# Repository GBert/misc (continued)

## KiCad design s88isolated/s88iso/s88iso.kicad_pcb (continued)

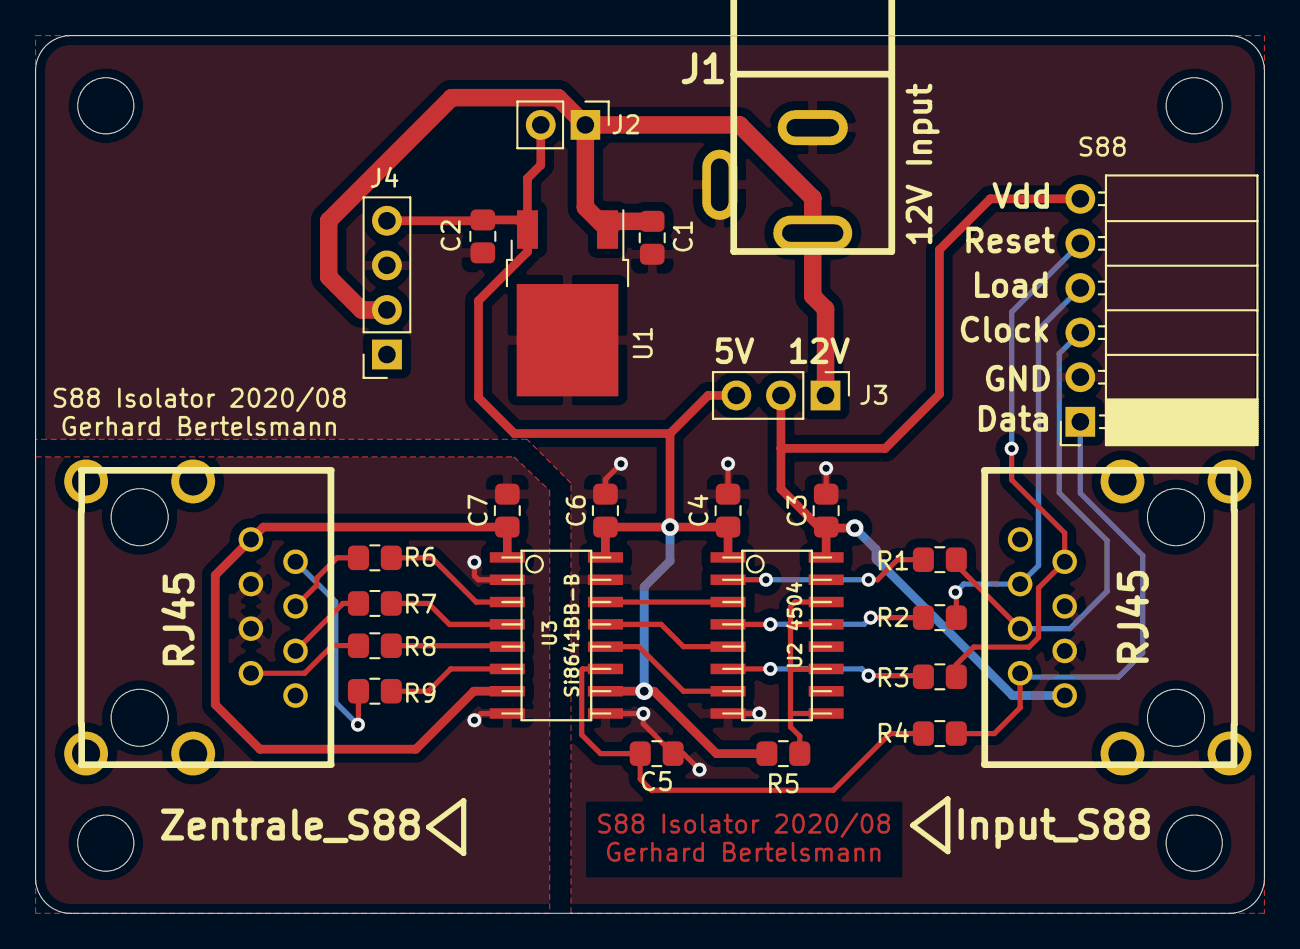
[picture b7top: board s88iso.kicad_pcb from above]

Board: 2 copper layers, 70.0 x 50.0 mm, 26 parts (0 on the bottom side), 26 nets.

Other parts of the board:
Input_S88: RJ45; megb8-8-Uni
Zentrale_S88: RJ45; megb8-8-Uni

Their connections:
+5V: Zentrale_S88.1; also elsewhere on the board
/Clock: Zentrale_S88.4; also elsewhere on the board
/Clock': Input_S88.4; also elsewhere on the board
/Data: Zentrale_S88.2; also elsewhere on the board
/Data': Input_S88.2; also elsewhere on the board
/PSLoad: Zentrale_S88.6; also elsewhere on the board
/PSLoad': Input_S88.6; also elsewhere on the board
/Reset: Zentrale_S88.7; also elsewhere on the board
/Reset': Input_S88.7; also elsewhere on the board
GND: Zentrale_S88.3, Zentrale_S88.5; also elsewhere on the board
GNDD: Input_S88.3, Input_S88.5; also elsewhere on the board
VDD: Input_S88.1; also elsewhere on the board

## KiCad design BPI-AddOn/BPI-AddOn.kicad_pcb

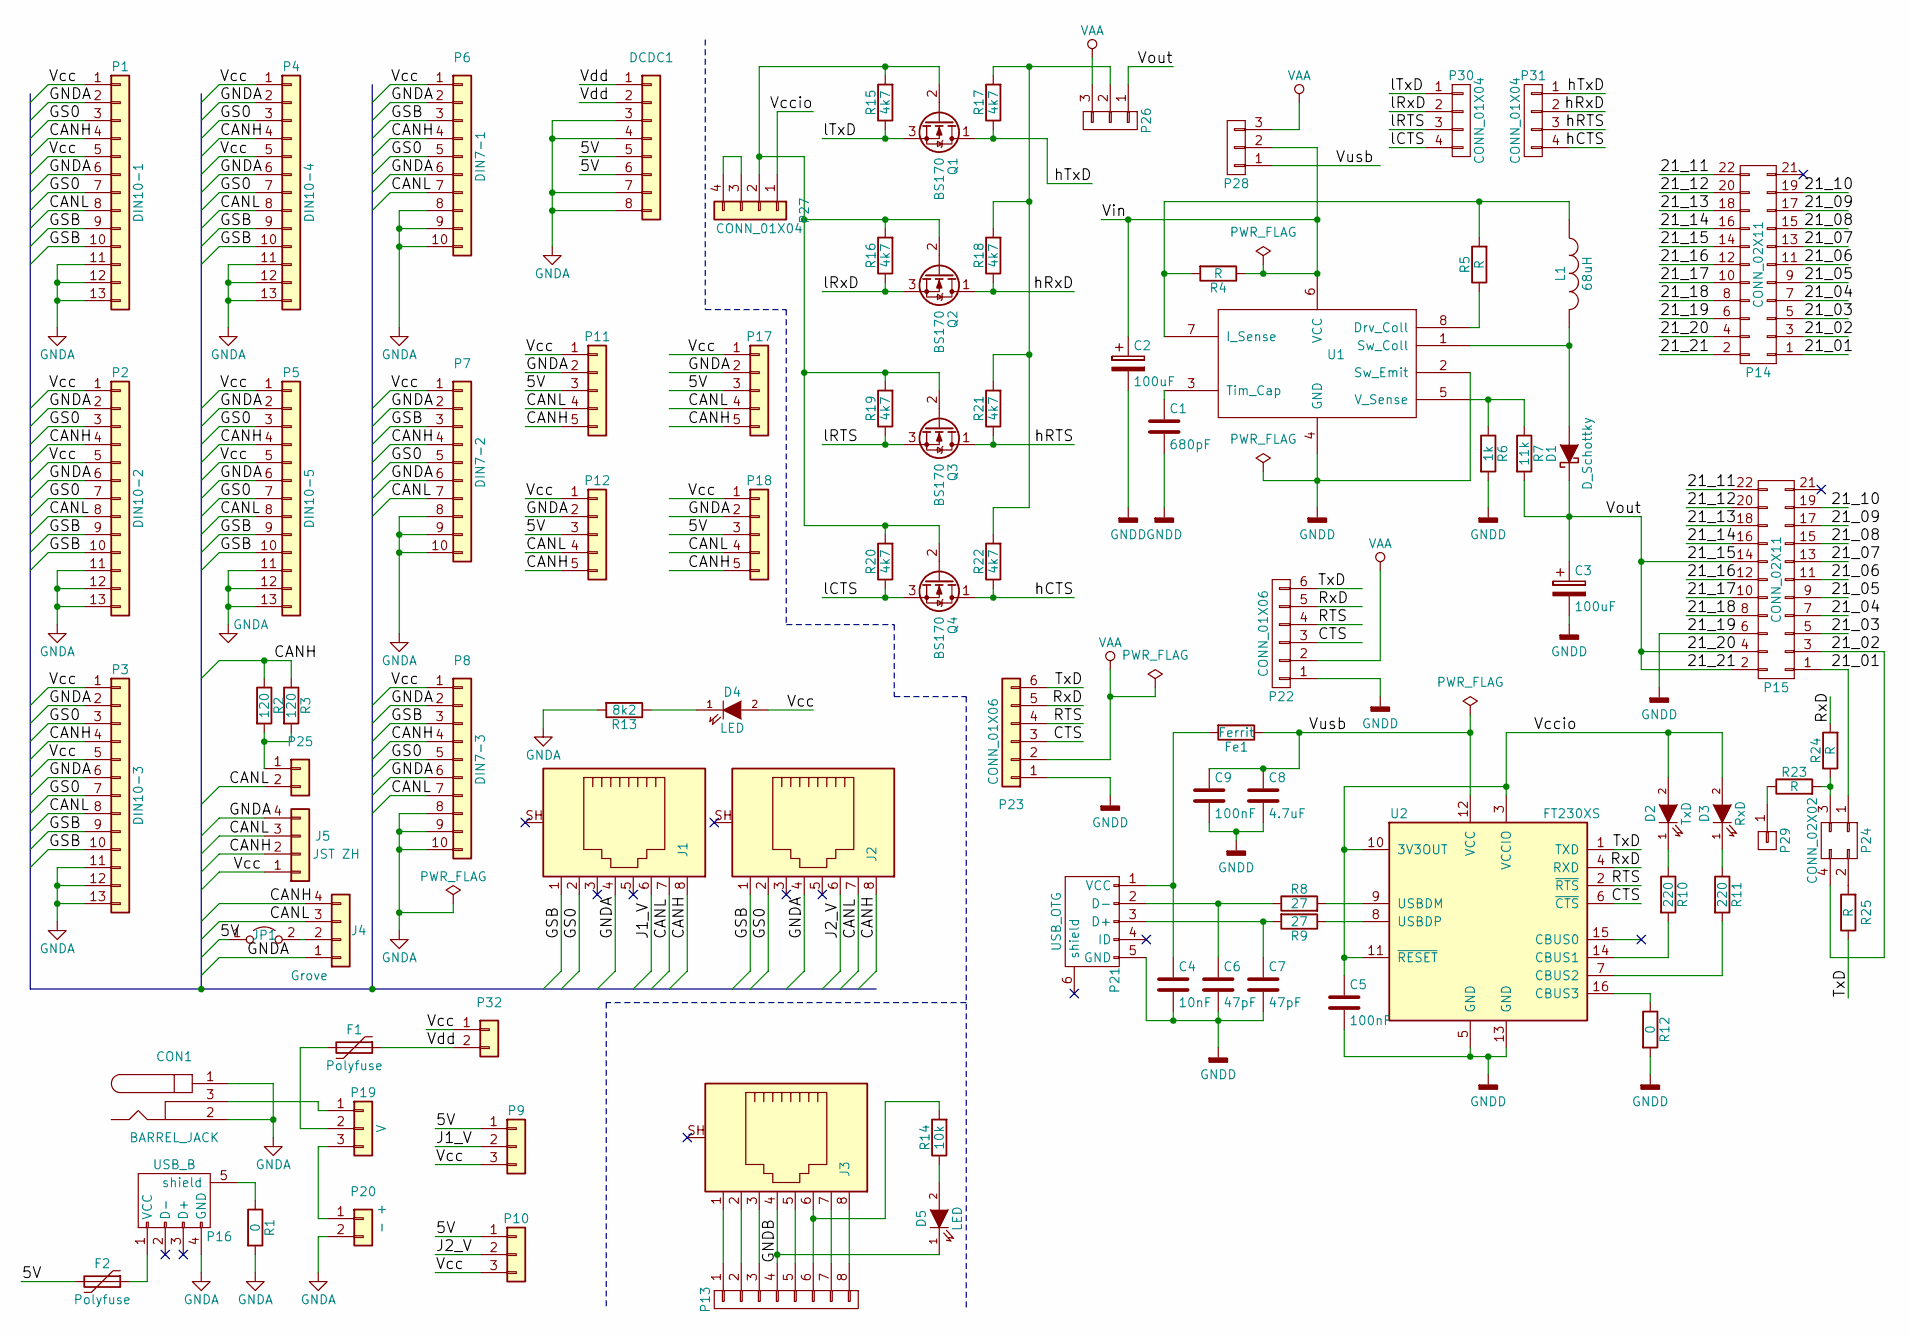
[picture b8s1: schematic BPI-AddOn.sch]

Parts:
C1: 680pF; cnp_3mm_disc
C2, C3: 100uF; CP_5x11mm
C4: 10nF; R_0805_HandSoldering
C5, C9: 100nF; R_0805_HandSoldering
C6, C7: 47pF; R_0805_HandSoldering
C8: 4.7uF; R_0805_HandSoldering
CON1: BARREL_JACK; dc_socket
D1: D_Schottky; Diode_DO-35_SOD27_Horizontal_RM10
D2: TxD; LED_0805
D3: RxD; LED_0805
D4, D5: LED; LED-5MM
DCDC1: DCDC-Conevrter; DCDC
F1, F2: Polyfuse; cnp_6mm_disc
Fe1: Ferrit; R_0805_HandSoldering
J1, J2, J3: RJ45; megb8-8
J4: Grove; grove-straight
J5: JST ZH; B4B-ZR
JP1: Jumper_2_Open; PinHeader_1x02_P2.54mm_Vertical
L1: 68uH; Neosid_Inductor_Sd14
P1: DIN10-1; minidin-10
P2: DIN10-2; minidin-10
P3: DIN10-3; minidin-10
P4: DIN10-4; minidin-10
P5: DIN10-5; minidin-10
P6: DIN7-1; minidin-7
P7: DIN7-2; minidin-7
P8: DIN7-3; minidin-7
P9, P10, P26, P28: CONN_01X03; Pin_Header_Straight_1x03
P11, P17, P18: CONN_01X05; Pin_Header_Straight_1x05
P12: CONN_01X05; pt_1,5-5-3,5-h
P13: CONN_01X08; Pin_Header_Straight_1x08
P14: CONN_02X11; Pin_Header_Straight_2x11
P15: CONN_02X11; ftsh-2211-01-l-dv
P16: USB_B; conn_usb_B
P19: V; Pin_Header_Straight_1x03
P20: - +; pt_1,5-2-3,5-h
P21: USB_OTG; conn_usb_B_mini_smd
P22: CONN_01X06; Pin_Header_Straight_1x06
P23: CONN_01X06; pt_1,5-6-3,5-h
P24: CONN_02X02; Pin_Header_Straight_2x02
P25, P32: CONN_01X02; Pin_Header_Straight_1x02
P27, P30, P31: CONN_01X04; Pin_Header_Straight_1x04
P29: CONN_01X01; Pin_Header_Straight_1x01
Q1, Q2, Q3, Q4: BS170; to92_3_flat
R1, R12: 0; R_0805_HandSoldering
R2: 120; R_1206_HandSoldering
R3: 120; RC05
R4, R5, R23, R24, R25: R; RC03
R6: 1k; RC03
R7: 11k; RC03
R8, R9: 27; R_0805_HandSoldering
R10, R11: 220; R_0805_HandSoldering
R13: 8k2; RC03
R14: 10k; RC05
R15, R16, R17, R18, R19, R20, R21, R22: 4k7; R_0805_HandSoldering
U1: MC34063; so-8
U2: FT230XS; ssop-16

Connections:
/5V: DCDC1.5, DCDC1.6, F2.2, JP1.1 (A), P9.1, P10.1, P11.3, P12.3, P17.3, P18.3
/21_01: P14.1, P15.1, P24.1
/21_02: P14.3, P15.3, P24.4
/21_03: P14.5, P15.5
/21_04: P14.7, P15.7
/21_05: P14.9, P15.9
/21_06: P14.11, P15.11
/21_07: P14.13, P15.13
/21_08: P14.15, P15.15
/21_09: P14.17, P15.17
/21_10: P14.19, P15.19
/21_11: P14.22, P15.22
/21_12: P14.20, P15.20
/21_13: P14.18, P15.18
/21_14: P14.16, P15.16
/21_15: C3.1, D1.1 (K), P14.2, P14.4, P14.14, P15.2, P15.4, P15.14, P26.1, R7.2
/21_16: P14.12, P15.12
/21_17: P14.10, P15.10
/21_18: P14.8, P15.8
/CANH: J1.8, J2.8, J4.4, J5.2, P1.4, P2.4, P3.4, P4.4, P5.4, P6.4, P7.4, P8.4, P11.5, P12.5, P17.5, P18.5, R2.1, R3.1
/CANL: J1.7, J2.7, J4.3, J5.3, P1.8, P2.8, P3.8, P4.8, P5.8, P6.7, P7.7, P8.7, P11.4, P12.4, P17.4, P18.4, P25.2
/CTS: P22.3, P23.3, U2.6 (~CTS)
/GNDB: D5.1 (K), J3.4, P13.4
/GS0: J1.2, J2.2, P1.3, P1.7, P2.3, P2.7, P3.3, P3.7, P4.3, P4.7, P5.3, P5.7, P6.5, P7.5, P8.5
/GSB: J1.1, J2.1, P1.9, P1.10, P2.9, P2.10, P3.9, P3.10, P4.9, P4.10, P5.9, P5.10, P6.3, P7.3, P8.3
/J1_V: J1.6, P9.2
/J2_V: J2.6, P10.2
/RTS: P22.4, P23.4, U2.2 (~RTS)
/RxD: P22.5, P23.5, R24.2, U2.4 (RXD)
/TxD: P22.6, P23.6, R25.1, U2.1 (TXD)
/Vcc: D4.2 (A), J5.1, P1.1, P1.5, P2.1, P2.5, P3.1, P3.5, P4.1, P4.5, P5.1, P5.5, P6.1, P7.1, P8.1, P9.3, P10.3, P11.1, P12.1, P17.1, P18.1, P32.1
/Vccio: C5.1, D2.2 (A), D3.2 (A), P27.1, U2.3 (VCCIO), U2.10 (3V3OUT), U2.11 (~RESET)
/Vdd: DCDC1.1, DCDC1.2, F1.1, P32.2
/Vin: C2.1, P28.2, R4.1, U1.6 (VCC)
/Vusb: C8.1, C9.1, Fe1.1, P28.1, U2.12 (VCC)
/hCTS: P31.4, Q4.1 (D), R22.1
/hRTS: P31.3, Q3.1 (D), R21.1
/hRxD: P31.2, Q2.1 (D), R18.1
/hTxD: P31.1, Q1.1 (D), R17.1
/lCTS: P30.4, Q4.3 (S), R20.1
/lRTS: P30.3, Q3.3 (S), R19.1
/lRxD: P30.2, Q2.3 (S), R16.1
/lTxD: P30.1, Q1.3 (S), R15.1
GNDA: CON1.1, CON1.2, DCDC1.3, DCDC1.4, DCDC1.7, DCDC1.8, J1.4, J2.4, J4.1, J5.4, P1.2, P1.6, P1.11, P1.12, P1.13, P2.2, P2.6, P2.11, P2.12, P2.13, P3.2, P3.6, P3.11, P3.12, P3.13, P4.2, P4.6, P4.11, P4.12, P4.13, P5.2, P5.6, P5.11, P5.12, P5.13, P6.2, P6.6, P6.8, P6.9, P6.10, P7.2, P7.6, P7.8, P7.9, P7.10, P8.2, P8.6, P8.8, P8.9, P8.10, P11.2, P12.2, P16.4 (GND), P17.2, P18.2, P20.2, R1.2, R13.2
GNDD: C1.2, C2.2, C3.2, C4.2, C5.2, C6.2, C7.2, C8.2, C9.2, P14.6, P15.6, P21.5 (GND), P22.1, P23.1, R6.2, R12.2, U1.2 (Sw_Emit), U1.4 (GND), U2.5 (GND), U2.13 (GND)
unnamed: C1.1, U1.3 (Tim_Cap)
unnamed: C4.1, Fe1.2, P21.1 (VCC)
unnamed: C6.1, P21.2 (D-), R8.1
unnamed: C7.1, P21.3 (D+), R9.2
unnamed: CON1.3, P19.1
unnamed: D1.2 (A), L1.2, U1.1 (Sw_Coll)
unnamed: D2.1 (K), R10.1
unnamed: D3.1 (K), R11.1
unnamed: D4.1 (K), R13.1
unnamed: D5.2 (A), R14.1
unnamed: F1.2, P19.2
unnamed: F2.1, P16.1 (VCC)
unnamed: J3.1, P13.1
unnamed: J3.2, P13.2
unnamed: J3.3, P13.3
unnamed: J3.5, P13.5
unnamed: J3.6, P13.6, R14.2
unnamed: J3.7, P13.7
unnamed: J3.8, P13.8
unnamed: J4.2, JP1.2 (B)
unnamed: L1.1, R4.2, R5.2, U1.7 (I_Sense)
unnamed: P16.5 (shield), R1.1
unnamed: P19.3, P20.1
unnamed: P24.2, R25.2
unnamed: P24.3, R23.2, R24.1
unnamed: P25.1, R2.2, R3.2
unnamed: P26.2, R17.2, R18.2, R21.2, R22.2
unnamed: P27.2, Q1.2 (G), Q2.2 (G), Q3.2 (G), Q4.2 (G), R15.2, R16.2, R19.2, R20.2
unnamed: P27.3, P27.4
unnamed: P29.1, R23.1
unnamed: R5.1, U1.8 (Drv_Coll)
unnamed: R6.1, R7.1, U1.5 (V_Sense)
unnamed: R8.2, U2.9 (USBDM)
unnamed: R9.1, U2.8 (USBDP)
unnamed: R10.2, U2.14 (CBUS1)
unnamed: R11.2, U2.7 (CBUS2)
unnamed: R12.1, U2.16 (CBUS3)
VAA: P22.2, P23.2, P26.3, P28.3

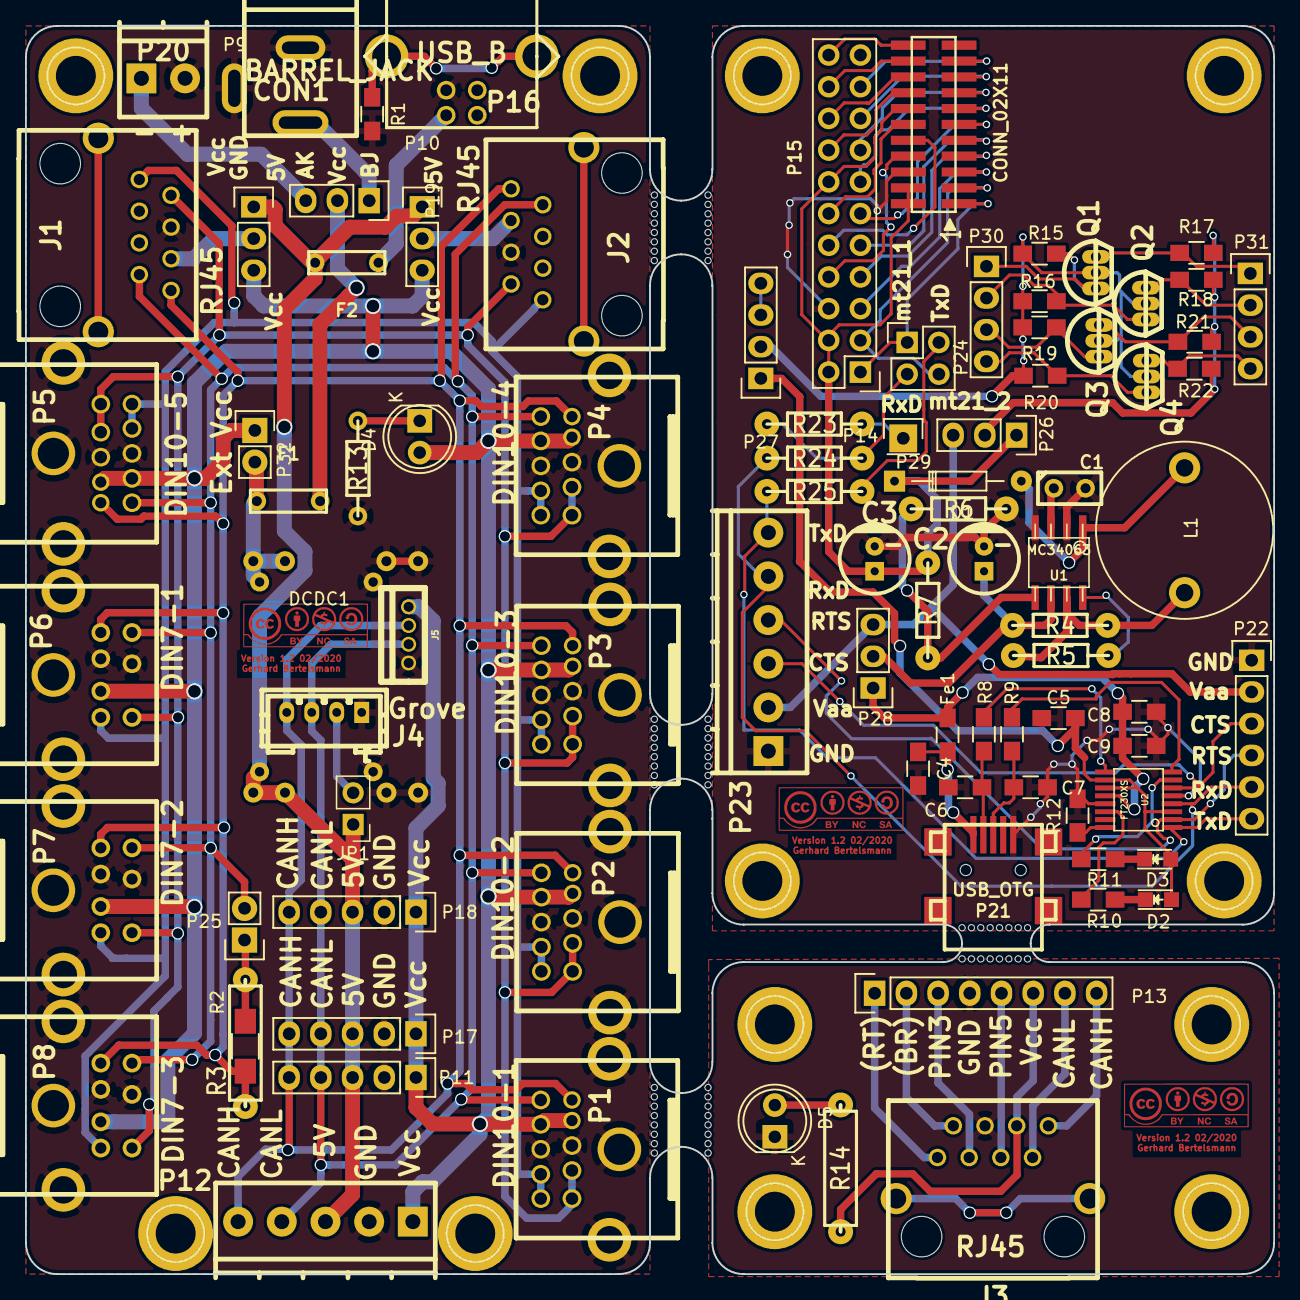
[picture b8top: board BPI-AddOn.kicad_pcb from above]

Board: 2 copper layers, 100.0 x 100.0 mm, 109 parts (0 on the bottom side), 83 nets.

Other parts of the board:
E05, E05#2, E05#3, E05#4, E05#5, E05#6, E05#7, E05#8: abortedge
REF1, REF2, REF3, REF3#2, REF3#3, REF4, REF4#2, REF4#3, REF4#4, REF4#5, REF4#6, REF4#7: 1pin

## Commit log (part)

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2021-03-24 change icon
2021-03-24 bump revision
2021-03-28 new version from Teddy
2021-03-28 new version bye Rainer Mueller
2021-04-03 fix compiling
2021-04-04 add WebServer/ResponseCsv.cpp
2021-04-04 add changes
2021-04-11 add actual TODO by Teddy
2021-04-16 reflect new version
2021-04-19 add missing files
2021-04-19 Update Makefile
2021-04-19 more generic makefile
2021-04-26 fix missing files
2021-04-30 fix reading magnet data
2021-04-30 fix also here the double freeing
2021-04-30 synchronize between can2udp and z21emu
2021-04-30 synchronize between can2udp and z21emu - 32 function tokens
2021-05-01 new version from Teddy - prepare for multiple loco controls (no new functionality)
2021-05-02 new version from Teddy - fix release of loco list
2021-05-02 update Makefile to new version
2021-05-04 calm down valgrind
2021-05-06 work again on mfx link
2021-05-06 new version of mfx-link
2021-05-06 smaller pics
2021-05-07 add picture where the cirrent sense transfprmer should be connected
2021-05-10 first try at JLCPCB
2021-05-11 fixed rotation / U3 still unclear
2021-05-11 some minimal silkscreen corrections
2021-05-11 P50x changes by Teddy
2021-05-12 new version by Teddy - using CAN responses
2021-05-12 fix U3
2021-05-12 only U1SM fiffers in orientation now
2021-05-12 increment version number to force update
2021-05-13 addded Changelog in readme
2021-05-14 add mfx decoding by Rainer
2021-05-14 fix compiler warning
2021-05-14 updated R17 against GND
2021-05-15 new MS2 ID 0x0033
2021-05-15 we need this file
2021-05-15 Improve viewport - by Teddy
2021-05-16 new version by Teddy
2021-05-18 fix getting F16-F31 from MS2 by Teddy
2021-05-20 new version from Teddy - add Drag&Drop
2021-05-21 new version from Teddy - more Drag&Drop work
2021-05-21 use 16ms timeout to cut off H-Bridge
2021-05-21 add some comments
2021-05-21 prepare ADC interrupt
2021-05-21 Fix pre and post scaler value
2021-05-21 ADC wip
2021-05-21 new version from Teddy - more Drag&Drop
2021-05-23 new production files for JLCPCB
2021-05-23 add tables
2021-05-24 new version from Teddy - allow shift&ctrl keys to rotate/move
2021-05-24 add Reichelt BOM
2021-05-24 add BOM - wip
2021-05-24 BOM - wip
2021-05-25 add picture again
2021-05-25 beautify drawing
2021-05-26 ADC - wip
2021-05-27 fix GND plane for IO
2021-05-27 add actual pdf
2021-05-28 use a slightly higher ADC speed
2021-05-28 fix LCSC part number for 22 Ohm resistor
2021-05-29 use different ADC properties
2021-05-29 add +18V ADC input
2021-05-30 allign text
2021-05-30 aad more data
2021-06-01 add a comment
2021-06-04 add some modiing pictures for early revisions
2021-06-04 add some wiring pictures
2021-06-04 add some hints
2021-06-04 we don't use cs2.exe
2021-06-04 use different pic sizes correctly
2021-06-10 stm32-slcan:adapted to the latest library, cleaning up a possibly corrupted package read from a uart
2021-06-11 wip - probably the most complicated multichannel ADC ever ...
2021-06-11 minimize SENSE variation
2021-06-11 us bit fields
2021-06-14 gcc11 fix by Teddy
2021-06-17 add IRQ latency hint
2021-06-19 Fix P50x booster on/off by Teddy
2021-06-20 make some use of Timer0
2021-06-21 add E146781 using
2021-06-21 use table
2021-06-21 fix doc
2021-06-21 P82B715 not needed
2021-06-24 reflect new version in makefile
2021-06-25 new version from Teddy - reorganize protocol implementation
2021-06-28 add ESU files from Teddy
2021-06-28 add missing header
2021-07-02 add new schematic pdf
2021-07-02 xc8 firmware by Martin Krause
2021-07-04 some modifictaions from Martin Krause
2021-07-20 change resistors for voltage measurement as suggested by Martin K.
2021-07-20 add voltage measurement picture
2021-07-20 add voltage measurement picture - soldered
2021-07-20 a little bit alrger
2021-07-23 add missing file
2021-08-20 add XpressNet device (RS485 9N1) - wip
2021-08-25 fix ASCII schematic and UBAUD calculation
2021-08-25 add back srse2 files
2021-08-25 prepare XpressNet
2021-08-27 testing simple RS485 device with CP2104
2021-08-27 adress and data bits look better now, but there is a gap between address and first data byte
2021-08-27 add some remarks regarding CP2104 with RS485
2021-08-28 use option interface and be more verbose on failure
2021-08-28 try to use standard termios to set custom baudrate
2021-08-30 some messages are only one byte - don't need to waste time swichting from address to data mode
2021-09-11 reduce parity changes to speed up
2021-09-11 more XPN testing code - wip
2021-09-12 use Access ram - more XpressNet testing
2021-09-14 deocde the XPN init - wip
2021-09-14 simplify a little bit
2021-09-14 now in stage loco info
2021-09-14 show more data received from throttle
2021-09-14 loco settings seems to work but it's getting ugly ...
2021-09-14 easier debugging
2021-09-15 track on/off - wip
2021-09-15 more comments
2021-09-15 save power on/off
2021-09-16 power state handling - wip
2021-09-17 CAN power change will be send to XpressNet
2021-09-17 XPN power change to CAN - wip (something is wrong here)
2021-09-17 hex files bcak
2021-09-17 hex files back
2021-09-19 XPN power change to CAN fix
2021-09-19 reuse CAN event mechanismen for XpressNet -> CAN/UART
2021-10-24 add STM32 SLCAN back
2021-11-04 change U_in calc for 10k/1k8 divider
2021-11-24 partly SMD PCB
2021-11-26 add small pic
2021-12-01 make V1.6 for JLCPCB Assemly Service
2021-12-05 for Microchip forum
2021-12-11 add hint
2021-12-11 new JLCPCB assembly version V1.7
2021-12-21 add SMD JLCPCB V1.7 picture
2022-01-05 fix LCSC part numbers
2022-01-05 move CPL file
2022-01-06 why not to connect Railground to S88 ground
2022-01-17 fixing iTrain channel mechnismn
2022-01-17 update hex file
2022-01-18 backup 1.12 version
2022-02-18 add some 60174 pics
2022-02-27 add actual schematic pdf
2022-02-27 add Power supply hint
2022-02-28 add actual schamitc pdf
2022-03-08 add s88 pic
2022-04-12 test OpenScad
2022-06-16 add HEX file
2022-06-18 fix Makefile
2022-10-21 add DCDC converter - wip
2022-10-21 move components to satisfy DCDC requirements
2022-10-31 add pics
2022-11-07 new SRSEII JLCPCB production files Version 1.8
2022-11-08 add 3D pic of V1.8
2022-11-08 add small version of picture
2022-11-20 add new production ZIP
2022-12-08 remove old 3V3 DCDC
2022-12-21 keep HEX file
2022-12-21 new date
2023-01-22 fix schematic - no existing GND interconnect
2023-02-09 fix PIC placing
2023-02-09 fix PIC placing - back to 270 orientation
2023-02-09 add Gerber files
2023-02-09 move power supply text a little bit
2023-02-12 add universal CAN mini adpater
2023-02-15 add some LinkS88 pictures
2023-02-23 add some pics
2023-02-24 fix pin header description and use larger resistors
2023-02-24 add MS1 Slave / Pin 5 Vcc
2023-02-24 rename JP2 to MS1 Master
2023-02-25 add some MS1 extension pics
2023-02-25 add Chagelog
2023-02-26 move some description on the silkscreen
2023-02-26 add CAN Power description pic
2023-02-26 add LinkS88 with SRSEII pic
2023-02-27 Hinweis auf die Bauteil-Quellen
2023-03-03 add some GND vias
2023-03-06 add Pi Pico test programm
2023-03-15 add actual schematic
2023-03-16 add some conditional compiling for XPN and CAN LED
2023-03-16 new version 1.14 with power status on D2
2023-03-16 Update Changelog.md
    Add missing Version Description
2023-03-16 Update Changelog.md
    Fix typo
2023-03-18 use the NO_CAN_LED switch correctly
2023-03-29 fix part placement
2023-03-29 fix part placement - now
2023-04-17 add german translation doc
2023-04-20 switch to Kicad 6.0 and add schematic pdf
2023-09-18 add production file with 2mm pin header
2023-09-23 add setup picture with Pi CAN Hat and LinkS88
2023-11-22 replace 18uH with 15uH - JLCPCB doesn't have Sumida 18uH anymore
2023-11-22 JLCPCB is complaining about missing R13 in BOM
2023-11-22 change LCSC ordering number for L100 15uH
2023-12-01 save the outcomes here
2023-12-01 some basic stuff
2023-12-03 do the decompress as well
2023-12-03 get the filters test
2023-12-10 type filter for ports
2023-12-22 use functions
2023-12-22 use input option
2023-12-22 print ports or filters optional
2023-12-22 use f-string for printing
2023-12-22 sort output
2023-12-22 sort naturally
2023-12-22 sort list as well
2024-03-06 fix S88 ID
2024-03-06 add V1.1 firmware
2024-03-08 fix formatting an Version
2024-03-08 set ID to LinkS88 id
2024-03-09 prepare 0x22 S88
2024-03-09 increase version
2024-03-10 add eeprom routines
2024-03-11 make Device ID independent from HW ID
2024-03-11 fix event ID handling
2024-03-11 add HEX files
2024-03-11 chech Device ID on 0x22 Event Request
2024-03-24 update to KiCad 7.0 - wip
2024-03-26 use 18V symbol instead of 24V
2024-03-26 reorganize schematic
2024-04-11 git rid off warning
2024-04-13 add Omega2 sockets
2024-04-13 fix ERC/DRC errors and warnings / fix bom and placements
2024-04-13 fix local library issue
2024-04-13 switch 18pF caps from 0805 to 0603 for JLCPCB basic parts
2024-04-13 more cutting costs
2024-04-13 smaller fixes - mainly silkscreen
2024-04-13 isolate I2C
2024-04-16 15uH isn't available at JLCPCB - use 18uH instead
2024-04-29 add actual production file
2024-08-22 add pics here
2024-10-13 fix indent
2024-10-13 new version v1.15
2024-10-13 add Martins overflow avoidance
2024-11-25 various changes form M. Krause
2025-01-04 add v1.16 firmware
2025-01-04 new version 1.27
2025-01-04 change 2mm pin socket
2025-01-04 change 2mm pin socket - now
2025-01-17 add pictures here
2025-01-17 add missing pics
2025-12-13 small changes
2025-12-13 add new inlay
2026-01-08 make inlay height vaiable
2026-01-11 fix typo and add cd
2026-01-15 Inlay 2 update and picture
2026-01-15 small size pic of inlay
2026-01-15 move pictures to own dir
